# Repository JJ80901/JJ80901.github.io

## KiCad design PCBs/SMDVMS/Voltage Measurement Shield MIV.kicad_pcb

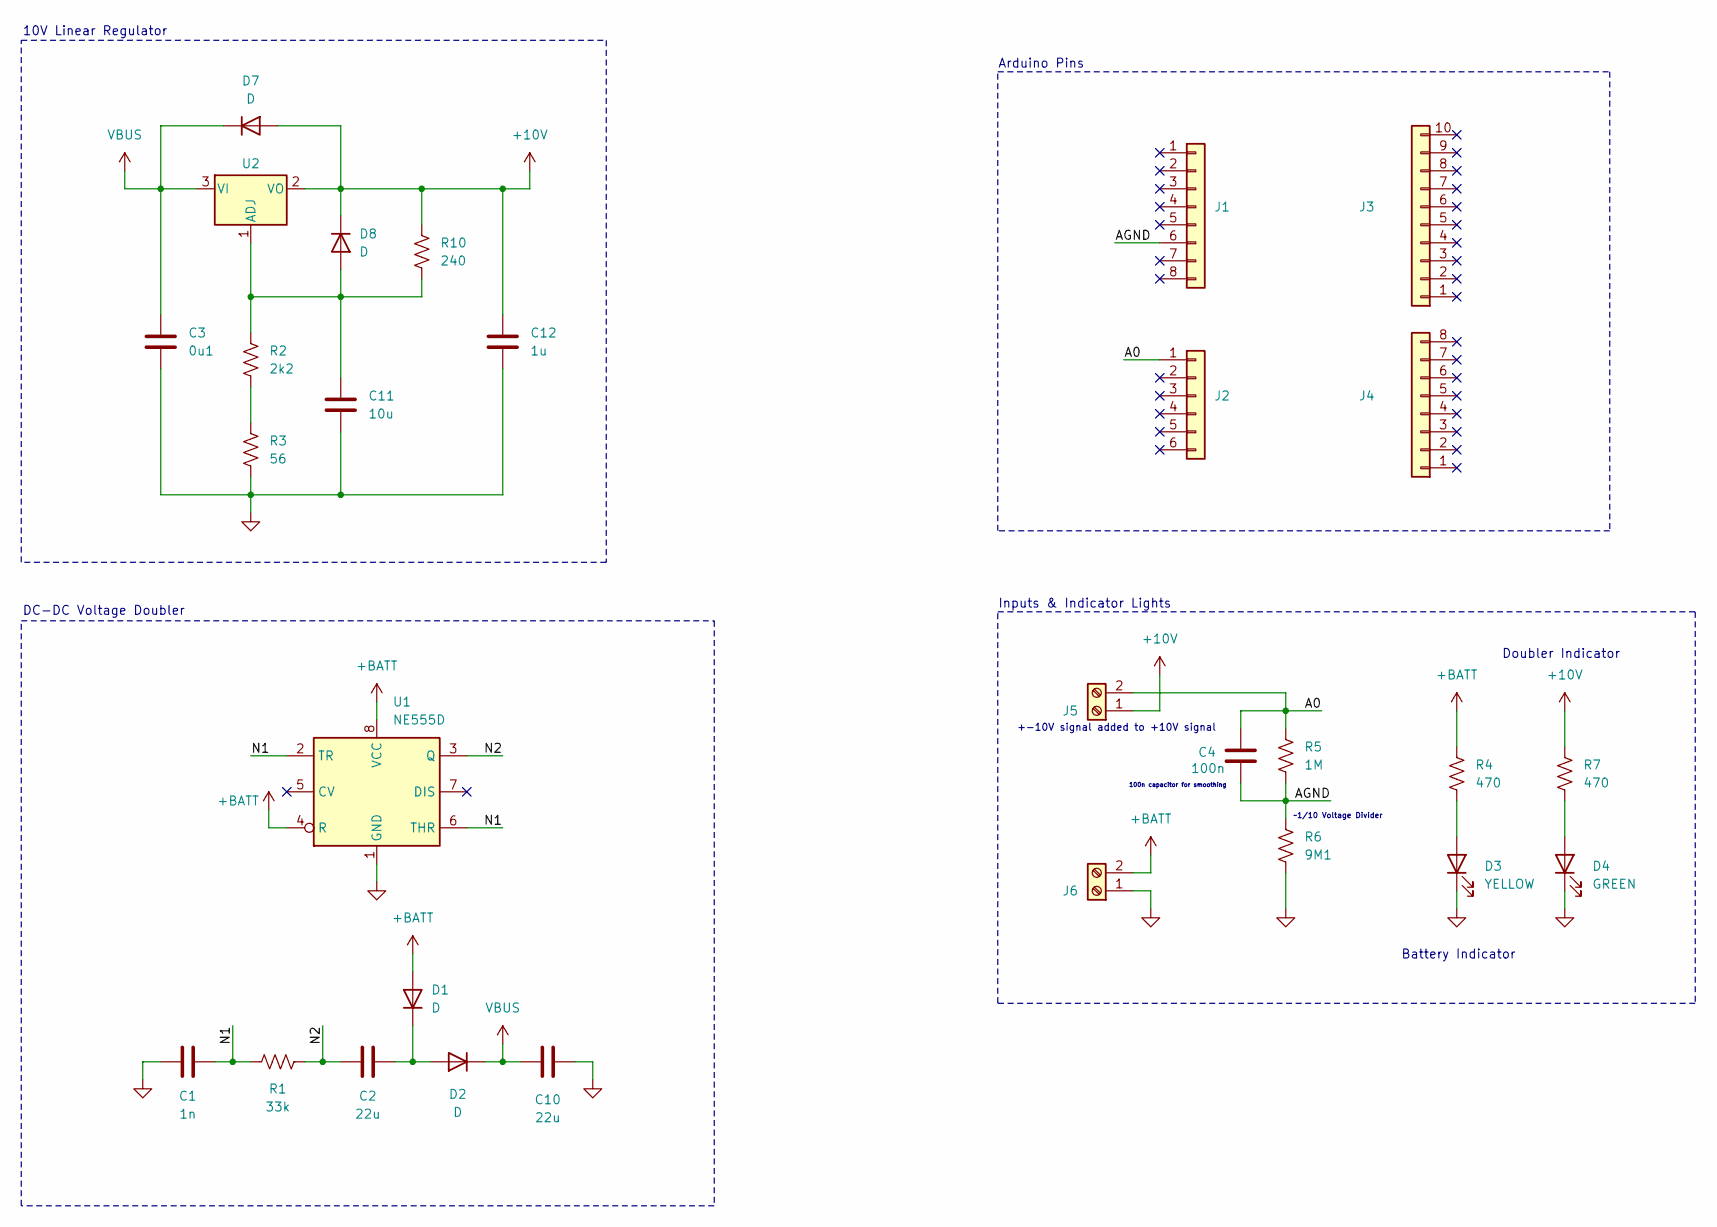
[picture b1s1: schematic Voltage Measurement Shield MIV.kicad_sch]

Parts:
C1: 1n; C_1206_3216Metric_Pad1.33x1.80mm_HandSolder
C2, C10: 22u; C_1206_3216Metric_Pad1.33x1.80mm_HandSolder
C3: 0u1; C_1206_3216Metric_Pad1.33x1.80mm_HandSolder
C4: 100n; C_1206_3216Metric_Pad1.33x1.80mm_HandSolder
C11: 10u; C_1206_3216Metric_Pad1.33x1.80mm_HandSolder
C12: 1u; C_1206_3216Metric_Pad1.33x1.80mm_HandSolder
D1, D2, D7, D8: D; D_1206_3216Metric_Pad1.42x1.75mm_HandSolder
D3: YELLOW; LED_1206_3216Metric_Pad1.42x1.75mm_HandSolder
D4: GREEN; LED_1206_3216Metric_Pad1.42x1.75mm_HandSolder
J1, J4: Conn_01x08; PinHeader_1x08_P2.54mm_Vertical
J2: Conn_01x06; PinHeader_1x06_P2.54mm_Vertical
J3: Conn_01x10; PinHeader_1x10_P2.54mm_Vertical
J5, J6: Screw_Terminal_01x02; PHOENIX_1935161
R1: 33k; R_1206_3216Metric_Pad1.30x1.75mm_HandSolder
R2: 2k2; R_1206_3216Metric_Pad1.30x1.75mm_HandSolder
R3: 56; R_1206_3216Metric_Pad1.30x1.75mm_HandSolder
R4, R7: 470; R_1206_3216Metric_Pad1.30x1.75mm_HandSolder
R5: 1M; R_1206_3216Metric_Pad1.30x1.75mm_HandSolder
R6: 9M1; R_1206_3216Metric_Pad1.30x1.75mm_HandSolder
R10: 240; R_1206_3216Metric_Pad1.30x1.75mm_HandSolder
U1: NE555D; SOIC-8_3.9x4.9mm_P1.27mm
U2: LM317_TO-220; TO-220-3_Vertical

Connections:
+10V: C12.1, D7.2 (A), D8.1 (K), J5.1, R7.1, R10.1, U2.2 (VO)
+BATT: D1.2 (A), J6.2, R4.1, U1.4 (R), U1.8 (VCC)
/A0: C4.1, J2.1, J5.2, R5.1
/AGND: C4.2, J1.6, R5.2, R6.1
/N1: C1.1, R1.2, U1.2 (TR), U1.6 (THR)
/N2: C2.2, R1.1, U1.3 (Q)
GND: C1.2, C3.2, C10.1, C11.2, C12.2, D3.1 (K), D4.1 (K), J6.1, R3.2, R6.2, U1.1 (GND)
unnamed: C2.1, D1.1 (K), D2.2 (A)
unnamed: D3.2 (A), R4.2
unnamed: D4.2 (A), R7.2
unnamed: C11.1, D8.2 (A), R2.1, R10.2, U2.1 (ADJ)
unnamed: R2.2, R3.1
VBUS: C3.1, C10.2, D2.1 (K), D7.1 (K), U2.3 (VI)

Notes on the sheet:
100n capacitor for smoothing
Inputs & Indicator Lights
Arduino Pins
Doubler Indicator
+-10V signal added to +10V signal
10V Linear Regulator
~1/10 Voltage Divider
DC-DC Voltage Doubler
Battery Indicator

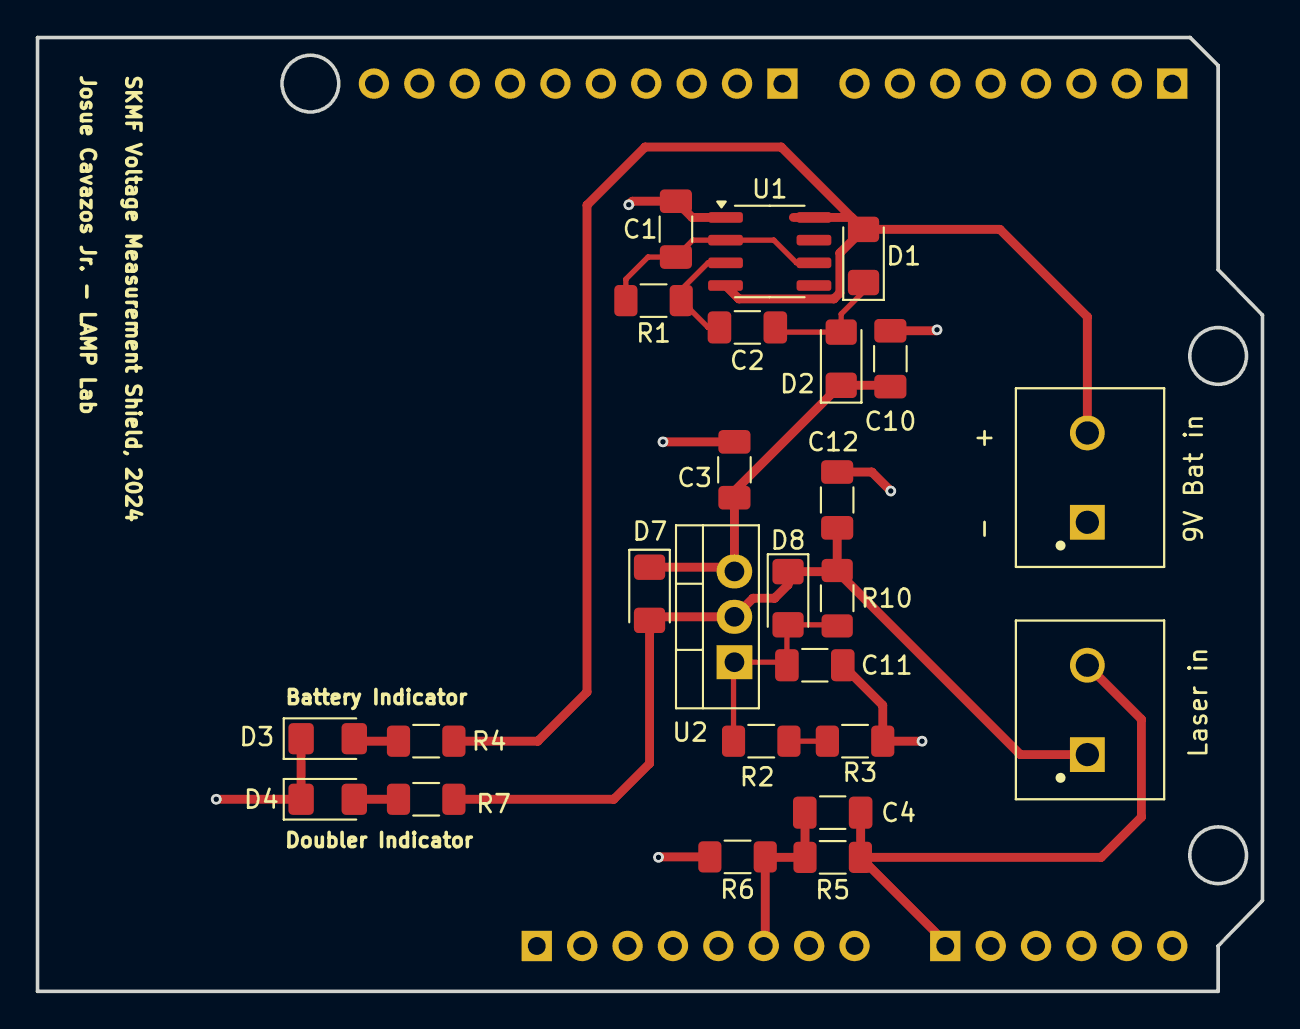
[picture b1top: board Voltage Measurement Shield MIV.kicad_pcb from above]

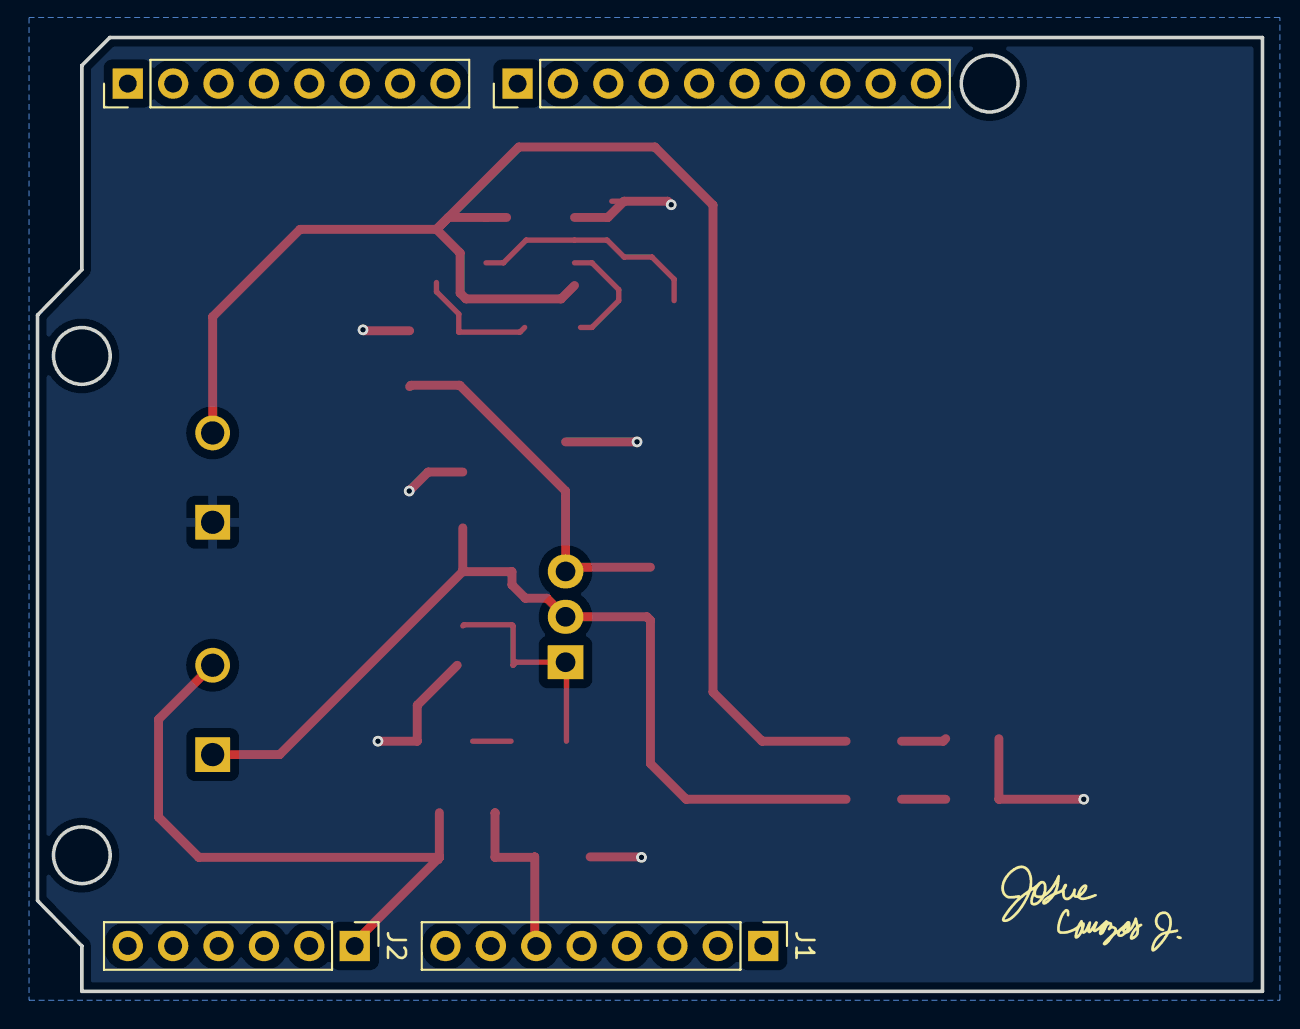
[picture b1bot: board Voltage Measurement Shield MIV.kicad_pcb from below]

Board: 2 copper layers, 68.6 x 53.4 mm, 29 parts (4 on the bottom side), 13 nets.

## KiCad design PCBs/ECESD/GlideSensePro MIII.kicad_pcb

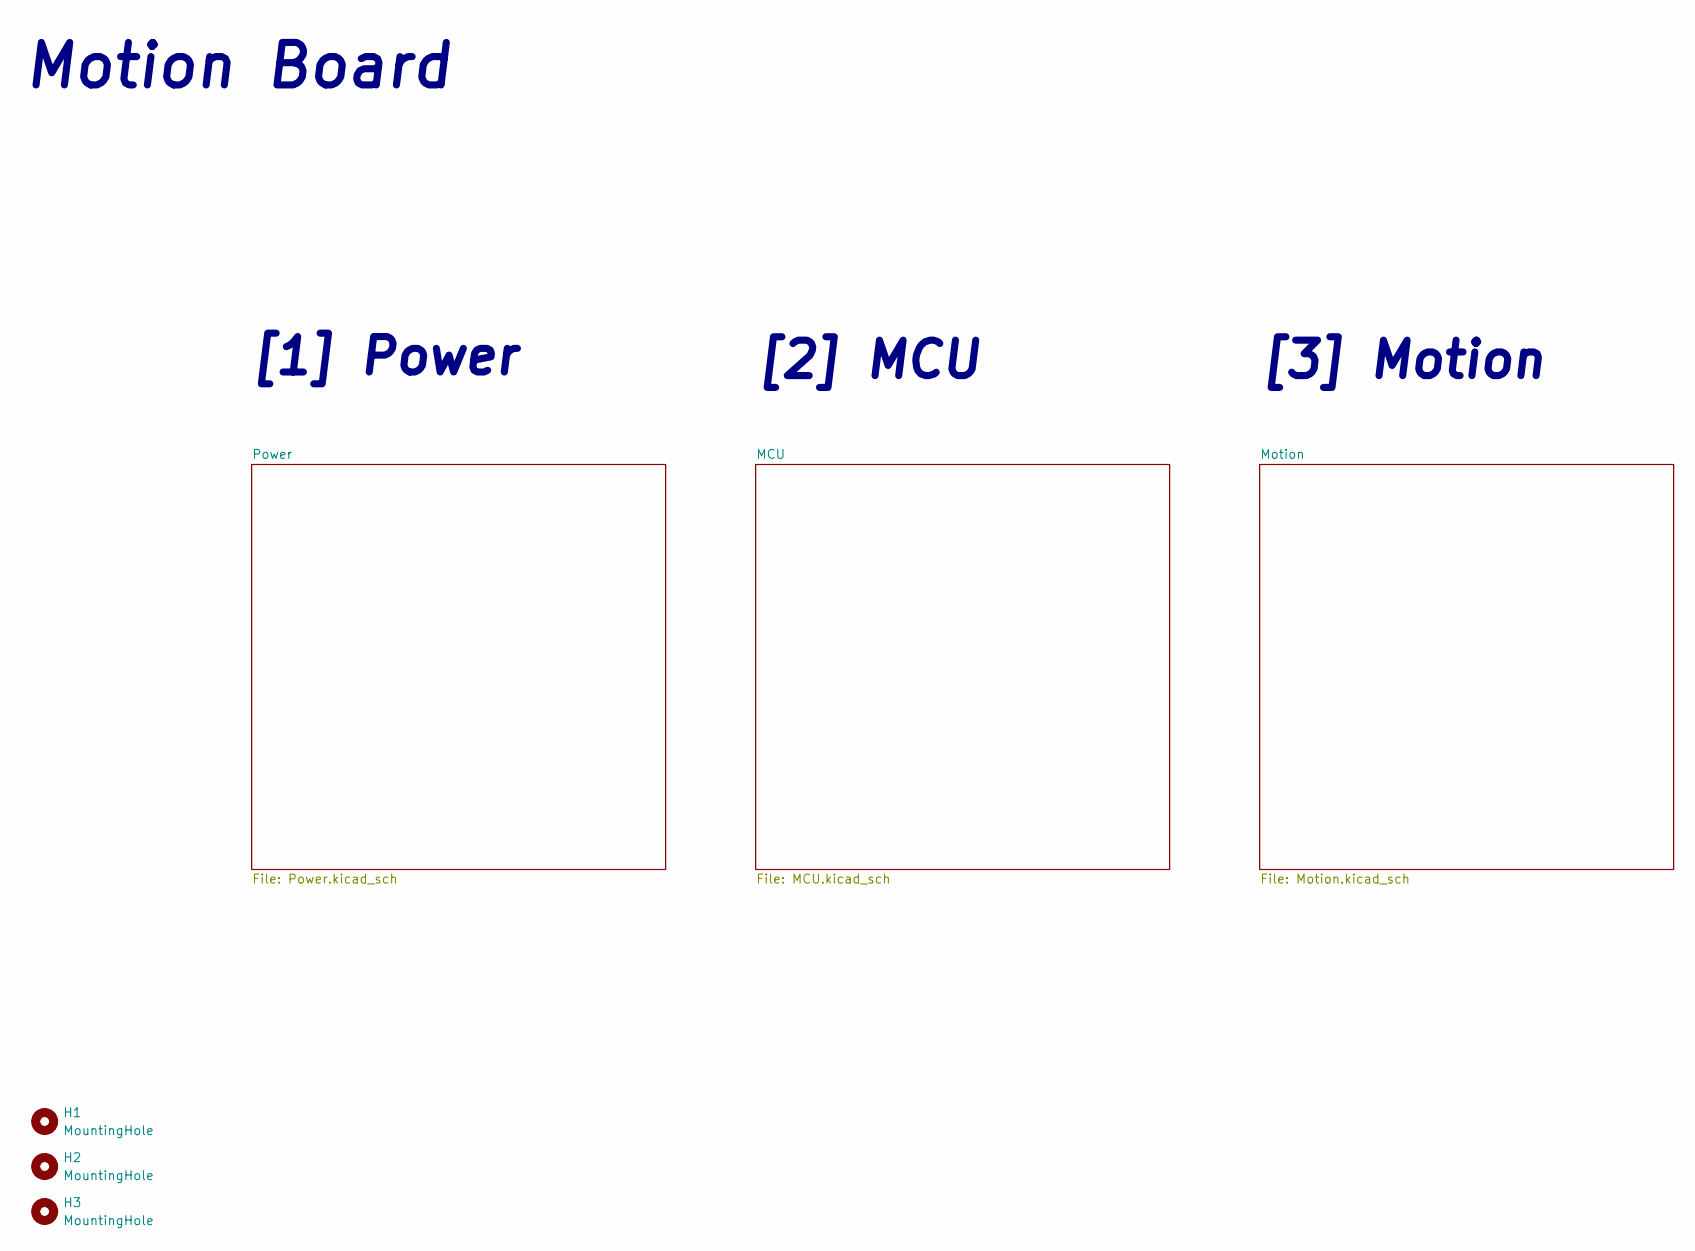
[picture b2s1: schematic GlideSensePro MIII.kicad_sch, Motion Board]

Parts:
H1, H2, H3: MountingHole; MountingHole_2.2mm_M2

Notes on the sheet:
[2] MCU
[1] Power
Motion Board
[3] Motion

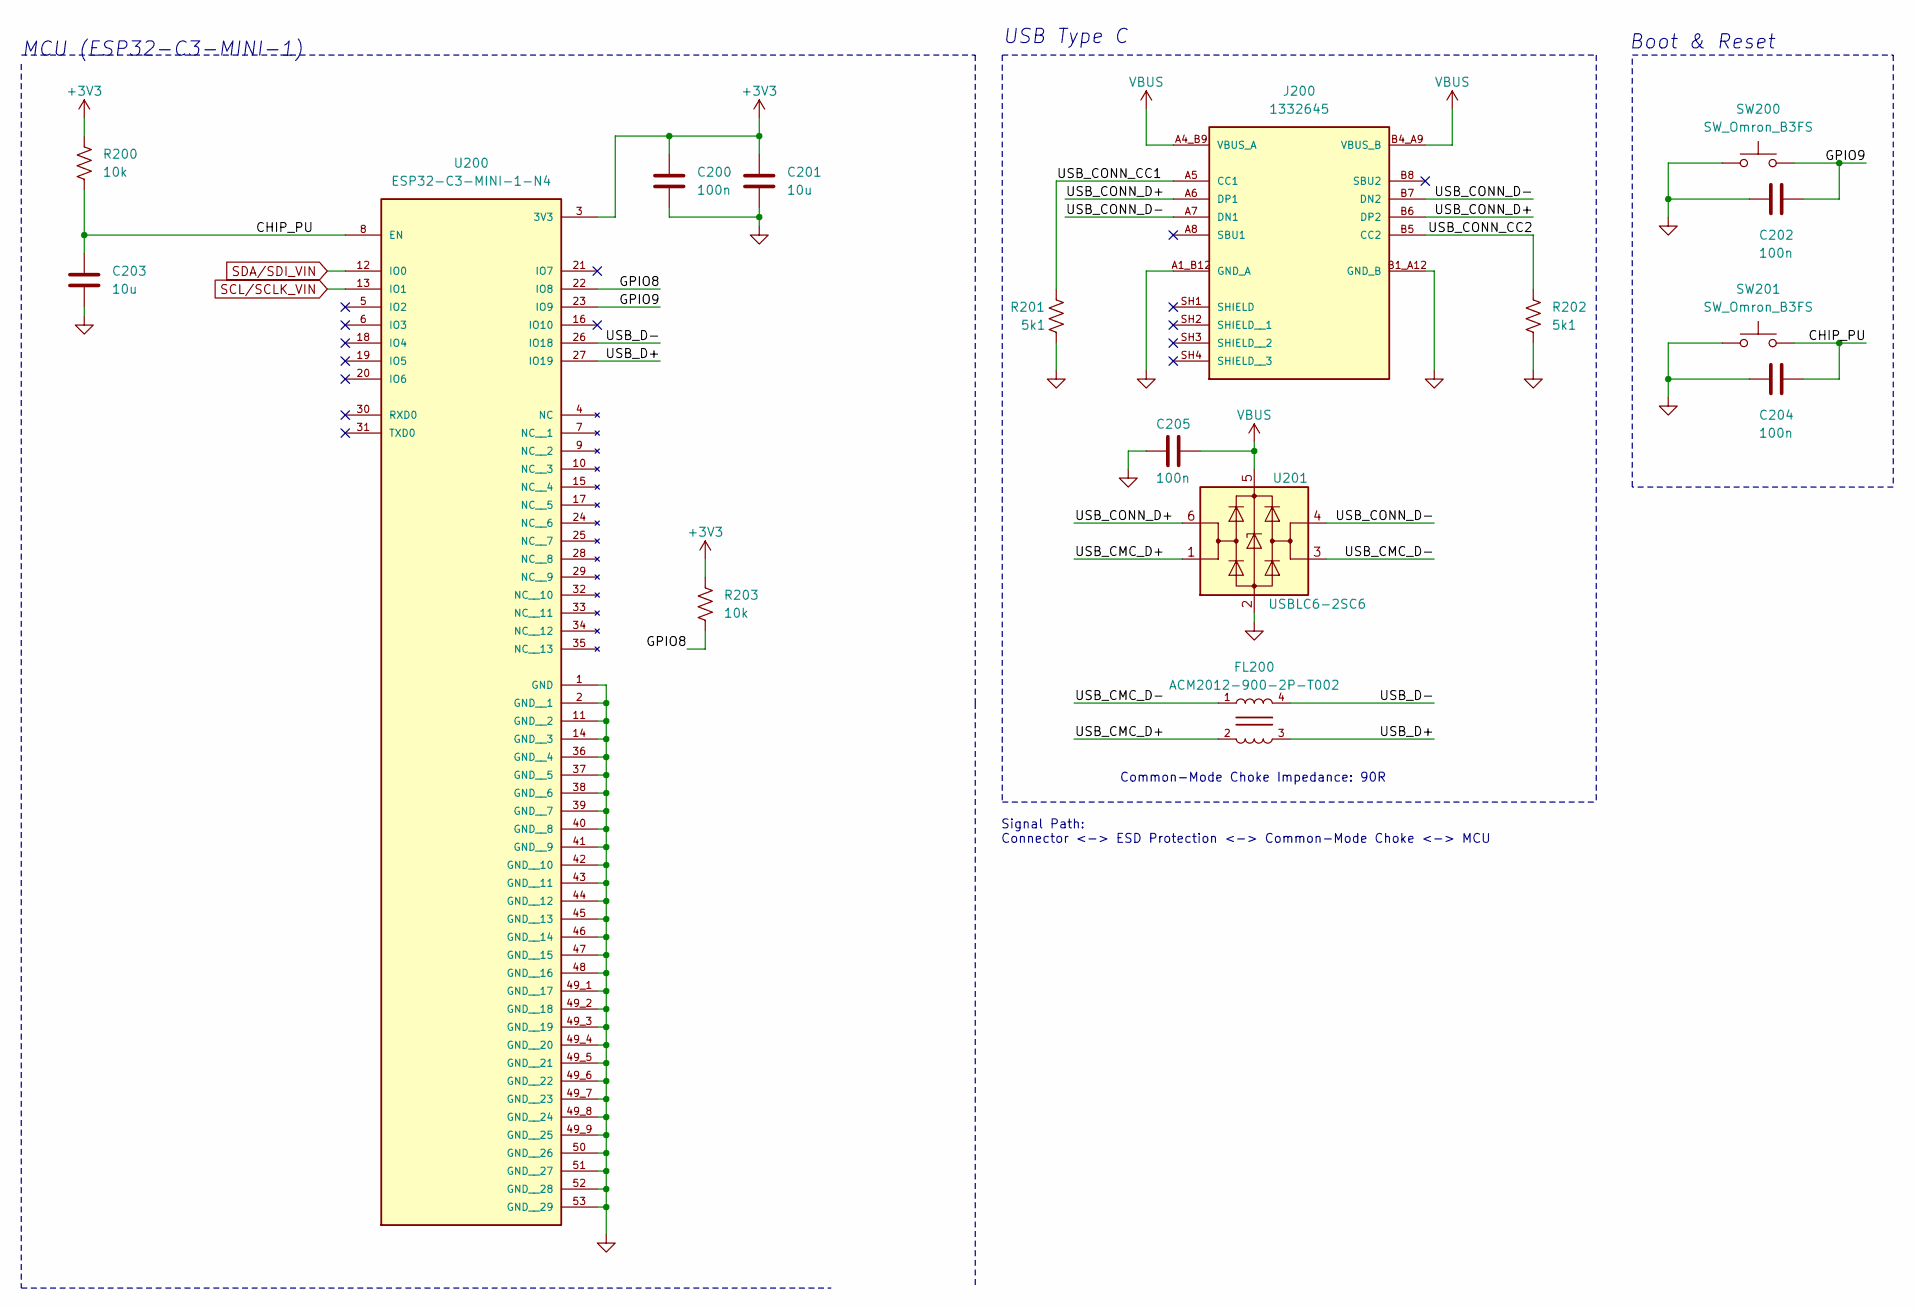
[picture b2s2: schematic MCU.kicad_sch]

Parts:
C200, C202, C204, C205: 100n; C_0603_1608Metric_Pad1.08x0.95mm_HandSolder
C201, C203: 10u; C_0603_1608Metric_Pad1.08x0.95mm_HandSolder
FL200: ACM2012-900-2P-T002; FIL_ACM2012-900-2P-T002
J200: 1332645; PHOENIX_1332645; PARTREV 17.01.2022
R200, R203: 10k; R_0603_1608Metric_Pad0.98x0.95mm_HandSolder
R201, R202: 5k1; R_0603_1608Metric_Pad0.98x0.95mm_HandSolder
SW200, SW201: SW_Omron_B3FS; SW_PUSH_6mm
U200: ESP32-C3-MINI-1-N4; XCVR_ESP32-C3-MINI-1-N4; PARTREV v1.0
U201: USBLC6-2SC6; SOT-23-6; LCSC Parrt # C7519

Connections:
+3V3: C200.1, C201.1, R200.1, R203.1, U200.3 (3V3); also elsewhere on the board
/MCU/CHIP_PU: C203.1, C204.1, R200.2, SW201.2, U200.8 (EN)
/MCU/GPIO8: R203.2, U200.22 (IO8)
/MCU/GPIO9: C202.1, SW200.2, U200.23 (IO9)
/MCU/USB_CMC_D+: FL200.2, U201.1 (I/O1)
/MCU/USB_CMC_D-: FL200.1, U201.3 (I/O2)
/MCU/USB_CONN_CC1: J200.A5 (CC1), R201.1
/MCU/USB_CONN_CC2: J200.B5 (CC2), R202.1
/MCU/USB_CONN_D+: J200.A6 (DP1), J200.B6 (DP2), U201.6 (I/O1)
/MCU/USB_CONN_D-: J200.A7 (DN1), J200.B7 (DN2), U201.4 (I/O2)
/MCU/USB_D+: FL200.3, U200.27 (IO19)
/MCU/USB_D-: FL200.4, U200.26 (IO18)
GND: C200.2, C201.2, C202.2, C203.2, C204.2, C205.2, J200.A1_B12 (GND_A), J200.B1_A12 (GND_B), R201.2, R202.2, SW200.1, SW201.1, U200.1 (GND), U200.2 (GND__1), U200.11 (GND__2), U200.14 (GND__3), U200.36 (GND__4), U200.37 (GND__5), U200.38 (GND__6), U200.39 (GND__7), U200.40 (GND__8), U200.41 (GND__9), U200.42 (GND__10), U200.43 (GND__11), U200.44 (GND__12), U200.45 (GND__13), U200.46 (GND__14), U200.47 (GND__15), U200.48 (GND__16), U200.49_1 (GND__17), U200.49_2 (GND__18), U200.49_3 (GND__19), U200.49_4 (GND__20), U200.49_5 (GND__21), U200.49_6 (GND__22), U200.49_7 (GND__23), U200.49_8 (GND__24), U200.49_9 (GND__25), U200.50 (GND__26), U200.51 (GND__27), U200.52 (GND__28), U200.53 (GND__29), U201.2 (GND); also elsewhere on the board
SCL/SCLK_VIN: U200.13 (IO1); also elsewhere on the board
SDA/SDI_VIN: U200.12 (IO0); also elsewhere on the board
VBUS: C205.1, J200.A4_B9 (VBUS_A), J200.B4_A9 (VBUS_B), U201.5 (VBUS); also elsewhere on the board

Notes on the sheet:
Signal Path: Connector <-> ESD Protection <-> Common-Mode Choke <-> MCU
USB Type C
Common-Mode Choke Impedance: 90R
Boot & Reset
MCU (ESP32-C3-MINI-1)

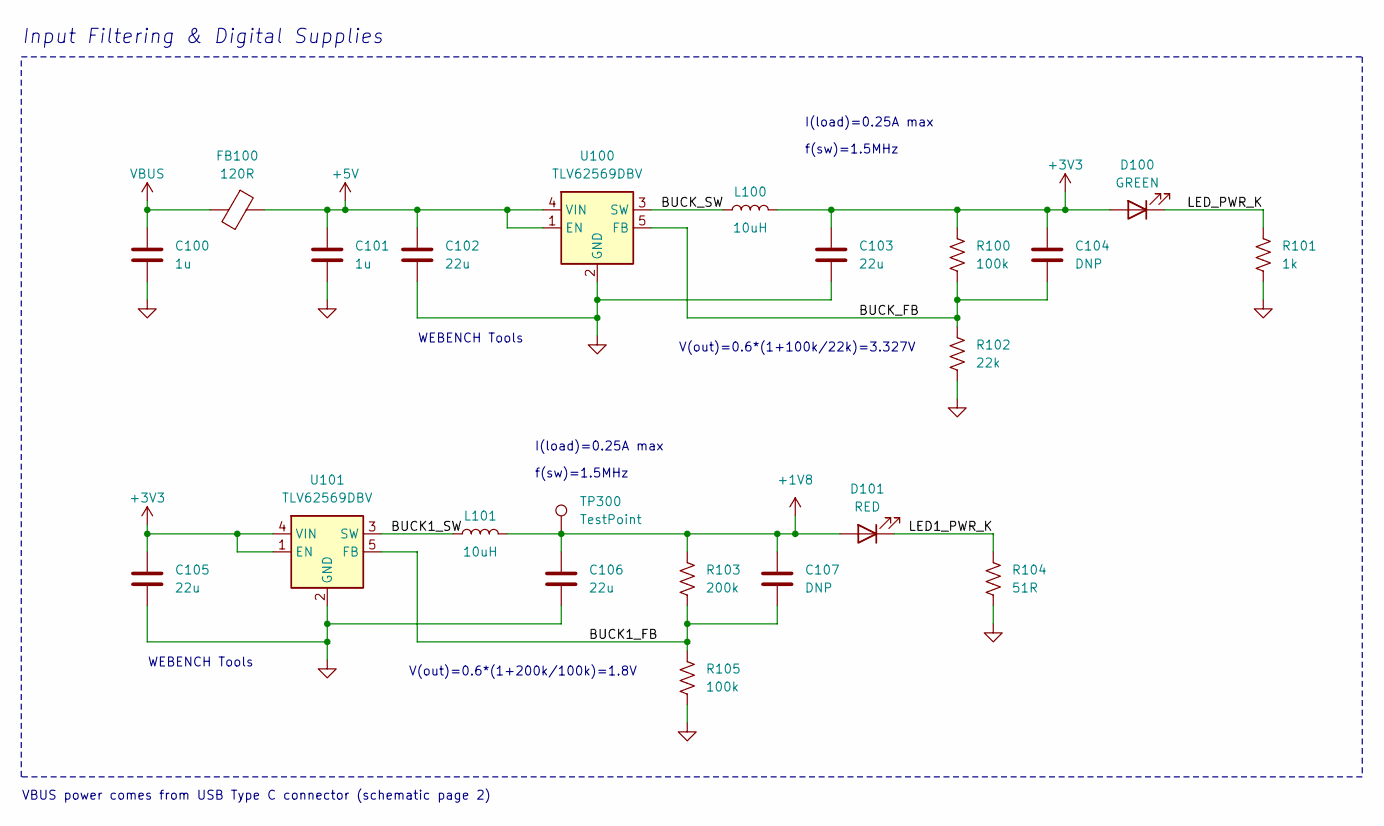
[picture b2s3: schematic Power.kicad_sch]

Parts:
C100, C101: 1u; C_0603_1608Metric_Pad1.08x0.95mm_HandSolder
C102, C103, C105, C106: 22u; C_0805_2012Metric_Pad1.18x1.45mm_HandSolder
C104, C107: DNP; C_0603_1608Metric_Pad1.08x0.95mm_HandSolder
D100: GREEN; LED_0603_1608Metric_Pad1.05x0.95mm_HandSolder
D101: RED; LED_0603_1608Metric_Pad1.05x0.95mm_HandSolder
FB100: 120R; L_0603_1608Metric_Pad1.05x0.95mm_HandSolder
L100, L101: 10uH; IND_VLS4015CX-100M-H
R100, R105: 100k; R_0603_1608Metric_Pad0.98x0.95mm_HandSolder
R101: 1k; R_0603_1608Metric_Pad0.98x0.95mm_HandSolder
R102: 22k; R_0603_1608Metric_Pad0.98x0.95mm_HandSolder
R103: 200k; R_0603_1608Metric_Pad0.98x0.95mm_HandSolder
R104: 51R; R_0603_1608Metric_Pad0.98x0.95mm_HandSolder
TP300: TestPoint; TestPoint_Pad_D1.0mm
U100, U101: TLV62569DBV; SOT-23-5

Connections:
+1V8: C106.1, C107.1, D101.2 (A), L101.2, R103.1, TP300.1; also elsewhere on the board
+3V3: C103.1, C104.1, C105.1, D100.2 (A), L100.2, R100.1, U101.1 (EN), U101.4 (VIN); also elsewhere on the board
+5V: C101.1, C102.1, FB100.1, U100.1 (EN), U100.4 (VIN)
/Power/BUCK1_FB: C107.2, R103.2, R105.1, U101.5 (FB)
/Power/BUCK1_SW: L101.1, U101.3 (SW)
/Power/BUCK_FB: C104.2, R100.2, R102.1, U100.5 (FB)
/Power/BUCK_SW: L100.1, U100.3 (SW)
/Power/LED1_PWR_K: D101.1 (K), R104.1
/Power/LED_PWR_K: D100.1 (K), R101.1
GND: C100.2, C101.2, C102.2, C103.2, C105.2, C106.2, R101.2, R102.2, R104.2, R105.2, U100.2 (GND), U101.2 (GND); also elsewhere on the board
VBUS: C100.1, FB100.2; also elsewhere on the board

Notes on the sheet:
f(sw)=1.5MHz
WEBENCH Tools
V(out)=0.6*(1+100k/22k)=3.327V
VBUS power comes from USB Type C connector (schematic page 2)
I(load)=0.25A max
V(out)=0.6*(1+200k/100k)=1.8V
Input Filtering & Digital Supplies

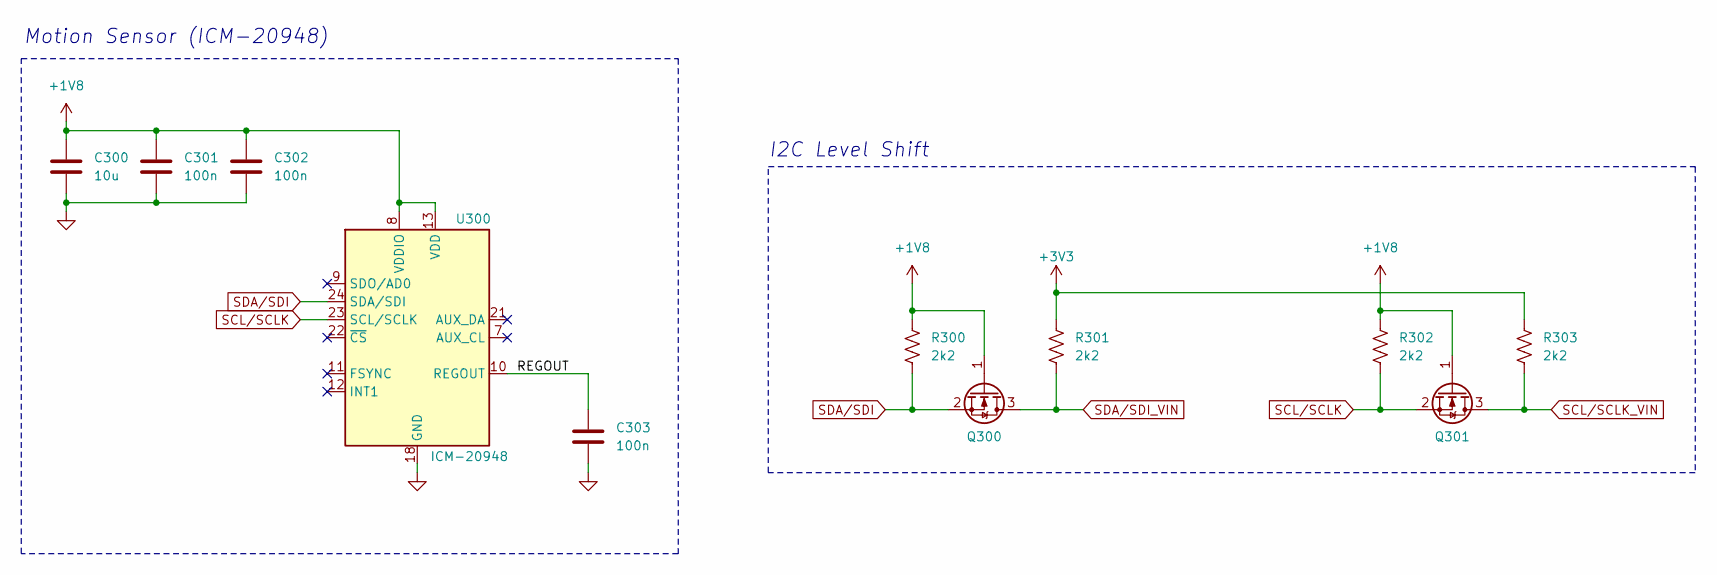
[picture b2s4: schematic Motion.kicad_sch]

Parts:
C300: 10u; C_0603_1608Metric_Pad1.08x0.95mm_HandSolder
C301, C302, C303: 100n; C_0603_1608Metric_Pad1.08x0.95mm_HandSolder
Q300, Q301: BSS138; SOT-23
R300, R301, R302, R303: 2k2; R_0603_1608Metric_Pad0.98x0.95mm_HandSolder
U300: ICM-20948; InvenSense_QFN-24_3x3mm_P0.4mm

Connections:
+1V8: C300.1, C301.1, C302.1, Q300.1 (G), Q301.1 (G), R300.1, R302.1, U300.8 (VDDIO), U300.13 (VDD); also elsewhere on the board
+3V3: R301.1, R303.1; also elsewhere on the board
/Motion/REGOUT: C303.1, U300.10 (REGOUT)
GND: C300.2, C301.2, C302.2, C303.2, U300.18 (GND), U300.20 (GND); also elsewhere on the board
SCL/SCLK: Q301.2 (S), R302.2, U300.23 (SCL/SCLK)
SCL/SCLK_VIN: Q301.3 (D), R303.2; also elsewhere on the board
SDA/SDI: Q300.2 (S), R300.2, U300.24 (SDA/SDI)
SDA/SDI_VIN: Q300.3 (D), R301.2; also elsewhere on the board

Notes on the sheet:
I2C Level Shift
Motion Sensor (ICM-20948)

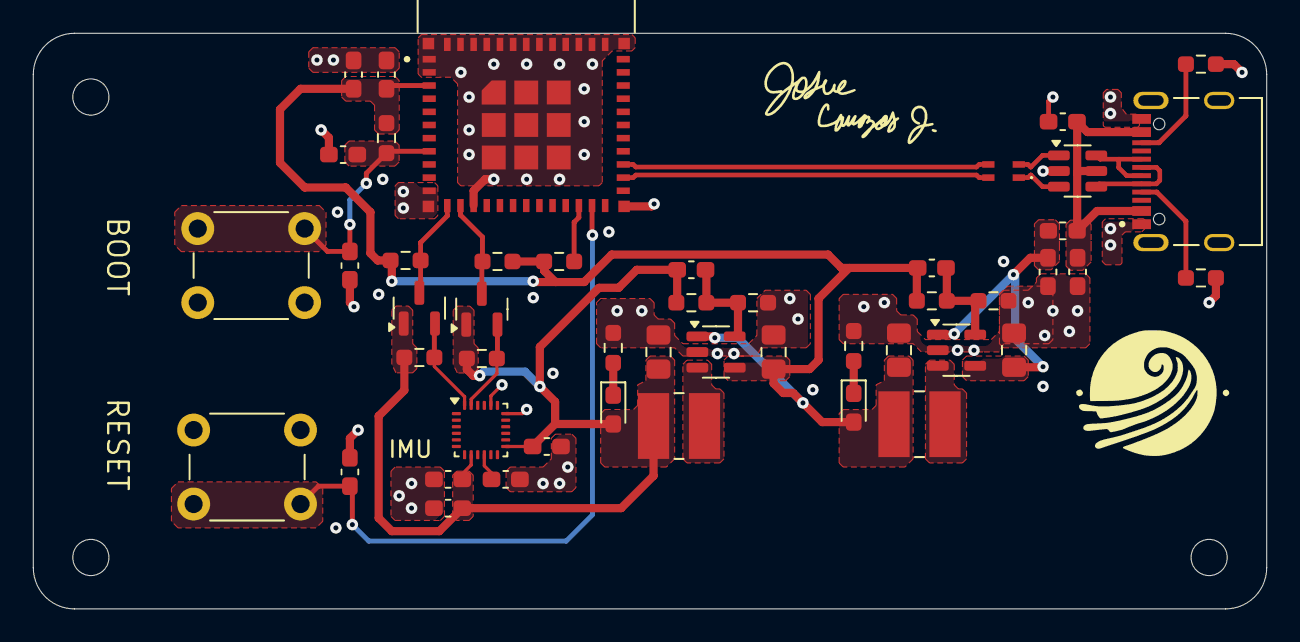
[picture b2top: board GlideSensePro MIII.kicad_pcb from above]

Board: 4 copper layers, 75.0 x 35.0 mm, 51 parts (0 on the bottom side), 27 nets.

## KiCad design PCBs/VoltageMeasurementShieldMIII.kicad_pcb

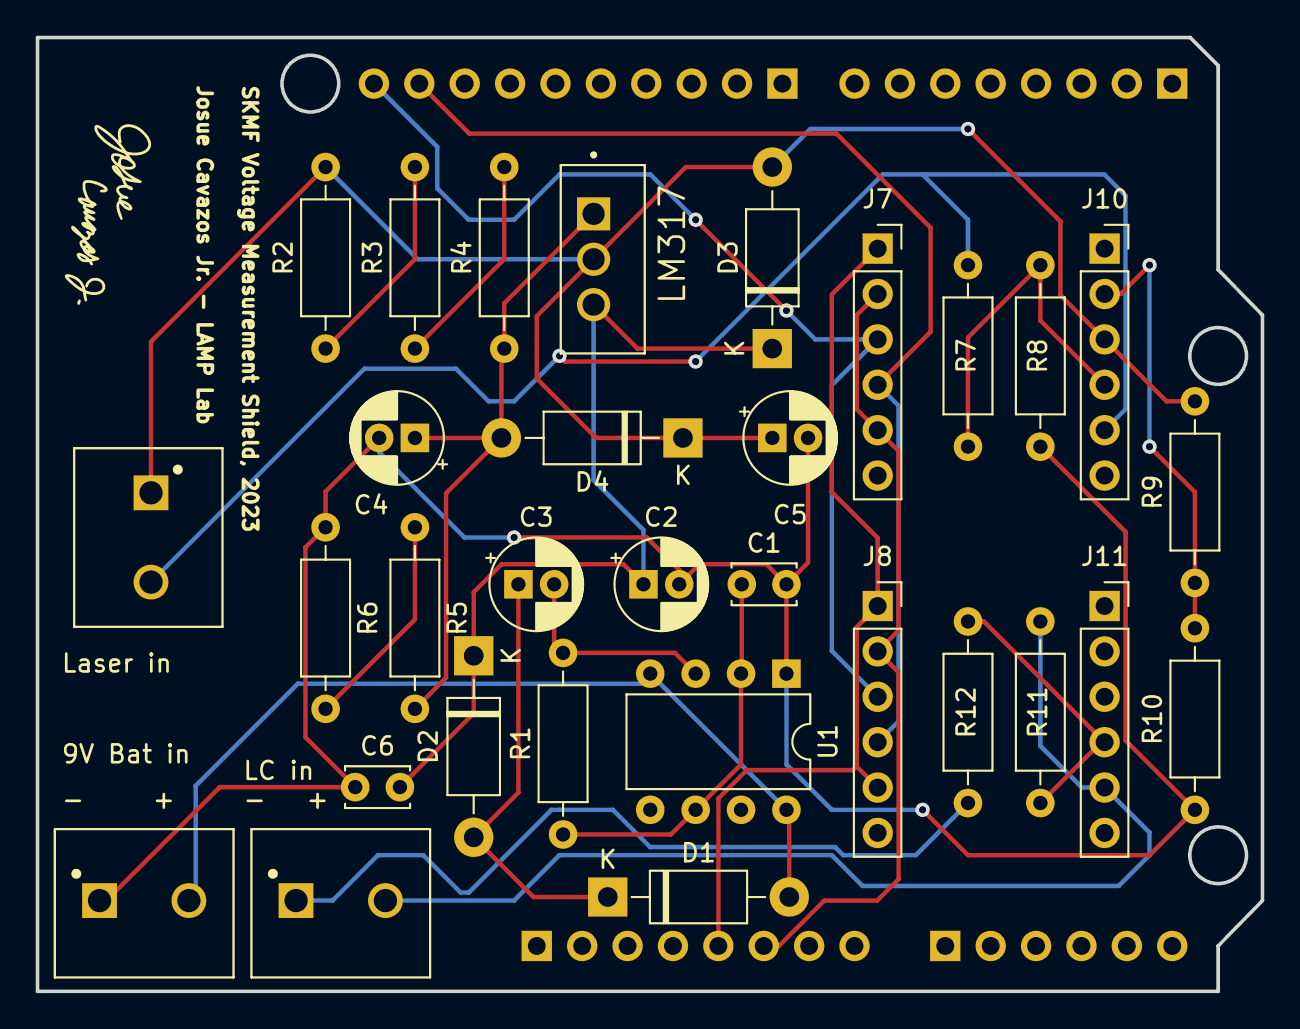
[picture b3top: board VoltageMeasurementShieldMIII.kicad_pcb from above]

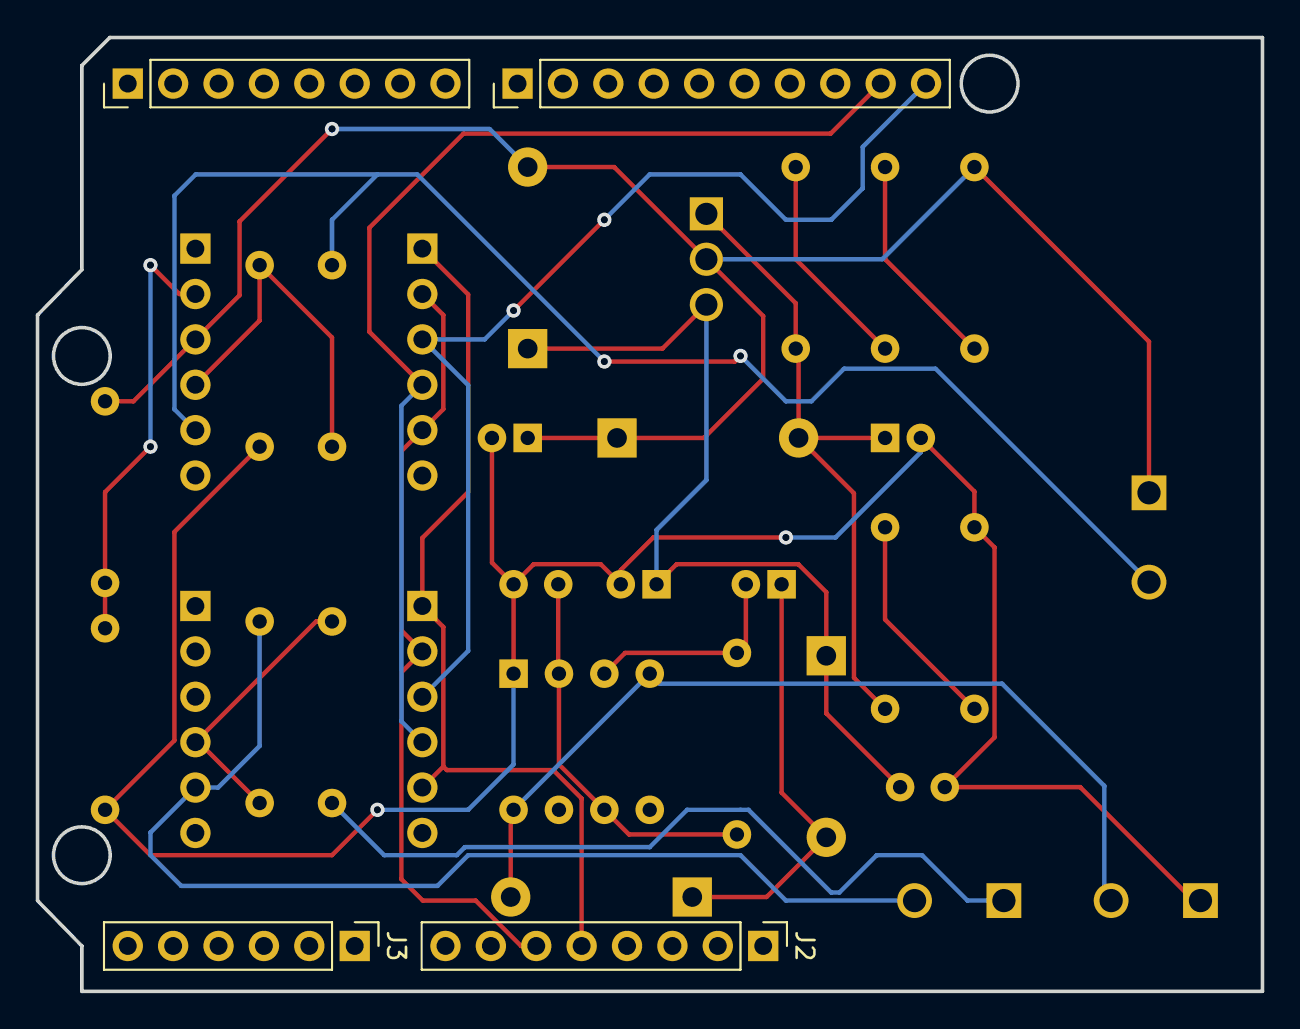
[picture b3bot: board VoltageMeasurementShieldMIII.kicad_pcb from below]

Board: 2 copper layers, 68.6 x 53.4 mm, 35 parts (4 on the bottom side), 21 nets.

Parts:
C1: 1nF; C_Disc_D3.4mm_W2.1mm_P2.50mm
C2, C3: 22uF; CP_Radial_D5.0mm_P2.00mm
C4: 10uF; CP_Radial_D5.0mm_P2.00mm
C5: 1uF; CP_Radial_D5.0mm_P2.00mm
C6: 0.1uF; C_Disc_D3.4mm_W2.1mm_P2.50mm
D1, D2, D3, D4: 1N4001; D_DO-41_SOD81_P10.16mm_Horizontal
J1, J6, J9: Screw_Terminal_01x02; PHOENIX_1935161
J2, J5: Conn_01x08; PinHeader_1x08_P2.54mm_Vertical
J3: Conn_01x06; PinHeader_1x06_P2.54mm_Vertical
J4: Conn_01x10; PinHeader_1x10_P2.54mm_Vertical
J7, J8, J10, J11: Conn_01x06; PinSocket_1x06_P2.54mm_Vertical
LM317: LM317T_NOPB; TO254P1054X470X1955-3
R1: 33k; R_Axial_DIN0207_L6.3mm_D2.5mm_P10.16mm_Horizontal
R2: 220; R_Axial_DIN0207_L6.3mm_D2.5mm_P10.16mm_Horizontal
R3, R4: 10; R_Axial_DIN0207_L6.3mm_D2.5mm_P10.16mm_Horizontal
R5: 2.2k; R_Axial_DIN0207_L6.3mm_D2.5mm_P10.16mm_Horizontal
R6: 56; R_Axial_DIN0207_L6.3mm_D2.5mm_P10.16mm_Horizontal
R7, R9, R11: 1k; R_Axial_DIN0207_L6.3mm_D2.5mm_P10.16mm_Horizontal
R8: 5.1k; R_Axial_DIN0207_L6.3mm_D2.5mm_P10.16mm_Horizontal
R10: 4.7k; R_Axial_DIN0207_L6.3mm_D2.5mm_P10.16mm_Horizontal
R12: 3.3k; R_Axial_DIN0207_L6.3mm_D2.5mm_P10.16mm_Horizontal
U1: LM555xN; DIP-8_W7.62mm

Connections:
/5V: J2.5, J7.1, J8.1, J8.5
/DC DC Voltage Doubler/GND: C1.2, C2.2, C4.2, C5.2, C6.1, J1.1, R6.1, R8.1, R10.1, U1.1 (GND)
/DC DC Voltage Doubler/N1: C1.1, R1.1, U1.2 (TR), U1.6 (THR)
/DC DC Voltage Doubler/N2: C3.2, R1.2, U1.3 (Q)
/DC DC Voltage Doubler/N3: C2.1, C6.2, D2.1 (K), D3.1 (K), LM317.3 (VIN)
/DC DC Voltage Doubler/VCC: D1.2 (A), J1.2, U1.4 (R), U1.8 (VCC)
/GND: J2.6, J7.2, J7.5, J8.2
/N1: J6.2, J10.5, R7.2
/N2: J10.4, R7.1, R8.2
/N3: C5.1, D3.2 (A), D4.1 (K), J6.1, J10.3, LM317.2 (VOUT), R2.2, R9.2
/N4: J10.2, R9.1, R10.2
/N5: J9.2, J11.5, R11.2
/N6: J11.4, R11.1, R12.2
/SCL: J4.10, J7.3, J8.3
/SDA: J4.9, J7.4, J8.4
unnamed: C3.1, D1.1 (K), D2.2 (A)
unnamed: C4.1, D4.2 (A), LM317.1 (ADJ), R4.1, R5.2
unnamed: J9.1, R12.1
unnamed: R2.1, R3.2
unnamed: R3.1, R4.2
unnamed: R5.1, R6.2

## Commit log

2022-12-30 Change image
2023-01-06 Changed to my portfolio in progress
2023-01-06 Added style
2023-05-11 Create images
2023-05-11 Update index.html
    Tested profile pic
2024-02-20 Update index.html
    Added kicanvas extension
2024-02-20 Update index.html
    Fixed syntax for embedding
2024-02-20 Update index.html
    Trying a better embedded file
2024-02-20 Update index.html
    Testing width of the embedded pcb window
2024-02-20 Update index.html
    Trying width again
2024-02-20 Update index.html
    Tried to wrap in paragraph
2024-02-20 Update style.css
    Changed paragraph style in css
2024-02-20 Update index.html
    Tried to add more attributes
2024-02-20 Update index.html
    Weird stuff
2024-02-20 Update style.css
    Max width
2024-02-20 Update style.css
    Header changes
2024-07-27 Added coming soon so that people know page is still being worked on
2025-01-22 Changed major and minors
2025-01-22 Removed PCB 3
2025-01-22 Changed first PCB
2025-01-22 Changed PCB 1 title
2025-01-22 Added new PCB files
2025-02-21 Changed wording and updated contact page
2025-02-21 Changed contact page
2025-02-21 Changed Board 1 summary
2025-02-21 Changed PCB 1
2025-02-21 Changed headings in contact page
2025-02-21 Simplified home page
2025-02-21 Changed PCB 2 description
2025-02-21 Changed wording on home page and contact heading
2025-02-21 Updated year
2025-02-21 Added repo link
2025-02-21 Changed github line
2025-02-21 Chagned about page
2025-02-21 Chagned repo style
2025-02-21 Changed main paragraph
2025-02-21 Chagnes
2025-02-21 changed hover
2025-02-21 Chagned styling
2025-02-21 Chagned github wording
2025-02-21 Fixed bug
2025-02-21 Added div
2025-02-21 Styled link
2025-02-21 Changed styling
2025-02-21 Changed list style
2025-02-21 Changed line
2025-02-21 Added support for mobile
2025-02-25 Added new PCB
2025-02-25 Fixed formatting
2025-02-25 Fixed layout
2025-02-25 Added PCB design files
2025-02-25 Fixed word format
2025-02-25 Fixed PCB Files
2025-02-26 Fixed wording'
